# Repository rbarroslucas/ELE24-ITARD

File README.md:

# ITA Rocket Design — Eletrônica

Repositório com códigos, esquemáticos e materiais de referência antigos do time de Eletrônica da ITA Rocket Design.

> Participação como membro (2023) e líder de eletrônica (2024 – meados de 2025).
> Os arquivos de PCB no KiCad **não foram publicados**.

---

## Estrutura do repositório

```
.
├── ELE2025/
│   ├── Código_ESP32/       # Módulo de telemetria (GPS + LoRa)
│   ├── Código_STM32/       # Placa principal de aviónica
│   ├── Minifogutes/        # Computador de voo para minifoguetes
│   ├── Receiver/           # Receptor LoRa em terra
│   ├── drop_test/          # Código para ensaio de impacto
│   └── Balanca/            # Software para ensaio estático de empuxo
├── PCB Design/
│   ├── Minifoguetes/       # Gerbers e esquemático (KiCad)
│   └── Transdutor/         # PCB do transmissor de pressão (KiCad)
├── Schematics/             # Esquemáticos em PDF (sistema ELE IPEV)
└── Exemplos/               # Códigos de referência
```

---

## Projetos

### Minifoguetes — Computador de Voo

Firmware para Arduino embarcado nos minifoguetes da equipe. Detecta decolagem por barômetro (BMP280), registra altitude e velocidade em cartão SD e aciona a recuperação (SKIB) automaticamente no apogeu.

**Hardware:** BMP280 · Cartão SD · LED · Buzzer · SKIB
**Arquivo:** `ELE2025/Minifogutes/minifog.ino`

```
Fluxo principal
├── calib()   — média inicial de altitude e velocidade no solo
├── solo()    — aguarda decolagem (Δh ≥ Hmin e |v| ≥ 1 m/s)
└── flight()  — registra dados e aciona SKIB no apogeu
```

---

### ELE2025 — Módulo ESP32 (Telemetria)

Responsável por coletar posição GPS e transmitir via LoRa (915 MHz) para a base em tempo real.

**Hardware:** ESP32 (Heltec) · GPS UART · LoRa 915 MHz · I2C
**Arquivos:** `ELE2025/Código_ESP32/Main/`

| Arquivo       | Função                                                             |
| ------------- | -------------------------------------------------------------------- |
| `Main.ino`  | Loop principal: lê GPS, monta pacote e envia via LoRa               |
| `GPS.ino`   | Leitura e parse do módulo GPS (latitude, longitude, altitude, hora) |
| `Radio.ino` | Configuração e envio LoRa                                          |
| `I2C.ino`   | Comunicação I2C com periféricos                                   |

---

### ELE2025 — Placa Principal STM32

Placa de aviónica com múltiplos sensores, comunicação SPI com o ESP32 e protocolo de instruções para controle de periféricos.

**Hardware:** STM32 · MPU9250 (IMU ×4) · BMP280 · HX711 (célula de carga) · Bateria · LED RGB · Buzzer · 6 chaves
**Arquivos:** `ELE2025/Código_STM32/Main/`

| Arquivo         | Função                                                   |
| --------------- | ---------------------------------------------------------- |
| `Main.ino`    | Setup e loop principal                                     |
| `MPU9250.ino` | Leitura do IMU (acelerômetro, giroscópio, magnetômetro) |
| `BMP280.ino`  | Leitura de pressão e altitude                             |
| `Hx711.ino`   | Leitura de célula de carga                                |
| `SPI.ino`     | Comunicação SPI com ESP32 via enum de instruções       |
| `Bat.ino`     | Monitoramento de tensão da bateria                        |

O protocolo SPI usa um enum de instruções (`Main.h`) para controlar todos os subsistemas remotamente.

---

### Receptor LoRa

Receptor em terra baseado em Heltec ESP32. Escuta na mesma frequência/configuração do transmissor e imprime os pacotes no Serial com RSSI e SNR.

**Arquivo:** `ELE2025/Receiver/receiver.ino`
**Frequência:** 915 MHz · SF7 · BW 125 kHz

---

### Balança — Ensaio Estático de Empuxo

Software Python para aquisição de dados durante ensaios estáticos do motor. Lê força (N) e tempo (ms) via serial, plota em tempo real e salva em CSV numerado automaticamente.

**Arquivo:** `ELE2025/Balanca/BalancaV3.4.py`
**Dependências:** `pyserial`, `matplotlib`

```bash
python BalancaV3.4.py
```

Os dados são salvos em `test/t<n>.csv`.

---

### Drop Test

Código de ensaio de impacto usando BMP280 para medir altitude e velocidade durante quedas controladas.

**Arquivos:** `ELE2025/drop_test/drop_test.ino`, `MedM.ino`

---

## PCBs

Os projetos KiCad **não estão publicados**. Os arquivos Gerber para fabricação estão disponíveis:

| PCB                     | Gerbers                                                         |
| ----------------------- | --------------------------------------------------------------- |
| Minifoguetes            | `PCB Design/Minifoguetes/minifoguetes/PCB/`                   |
| Transmissor de Pressão | `PCB Design/Transdutor/transmissor/pressure_transmissor_pcb/` |

---

## Esquemáticos

`Schematics/`— Sistema modular de aviónica composto por seis placas: Base, Energia, Interface, Processamento, Sensores e Telecom. Quase um cubesat 1u.

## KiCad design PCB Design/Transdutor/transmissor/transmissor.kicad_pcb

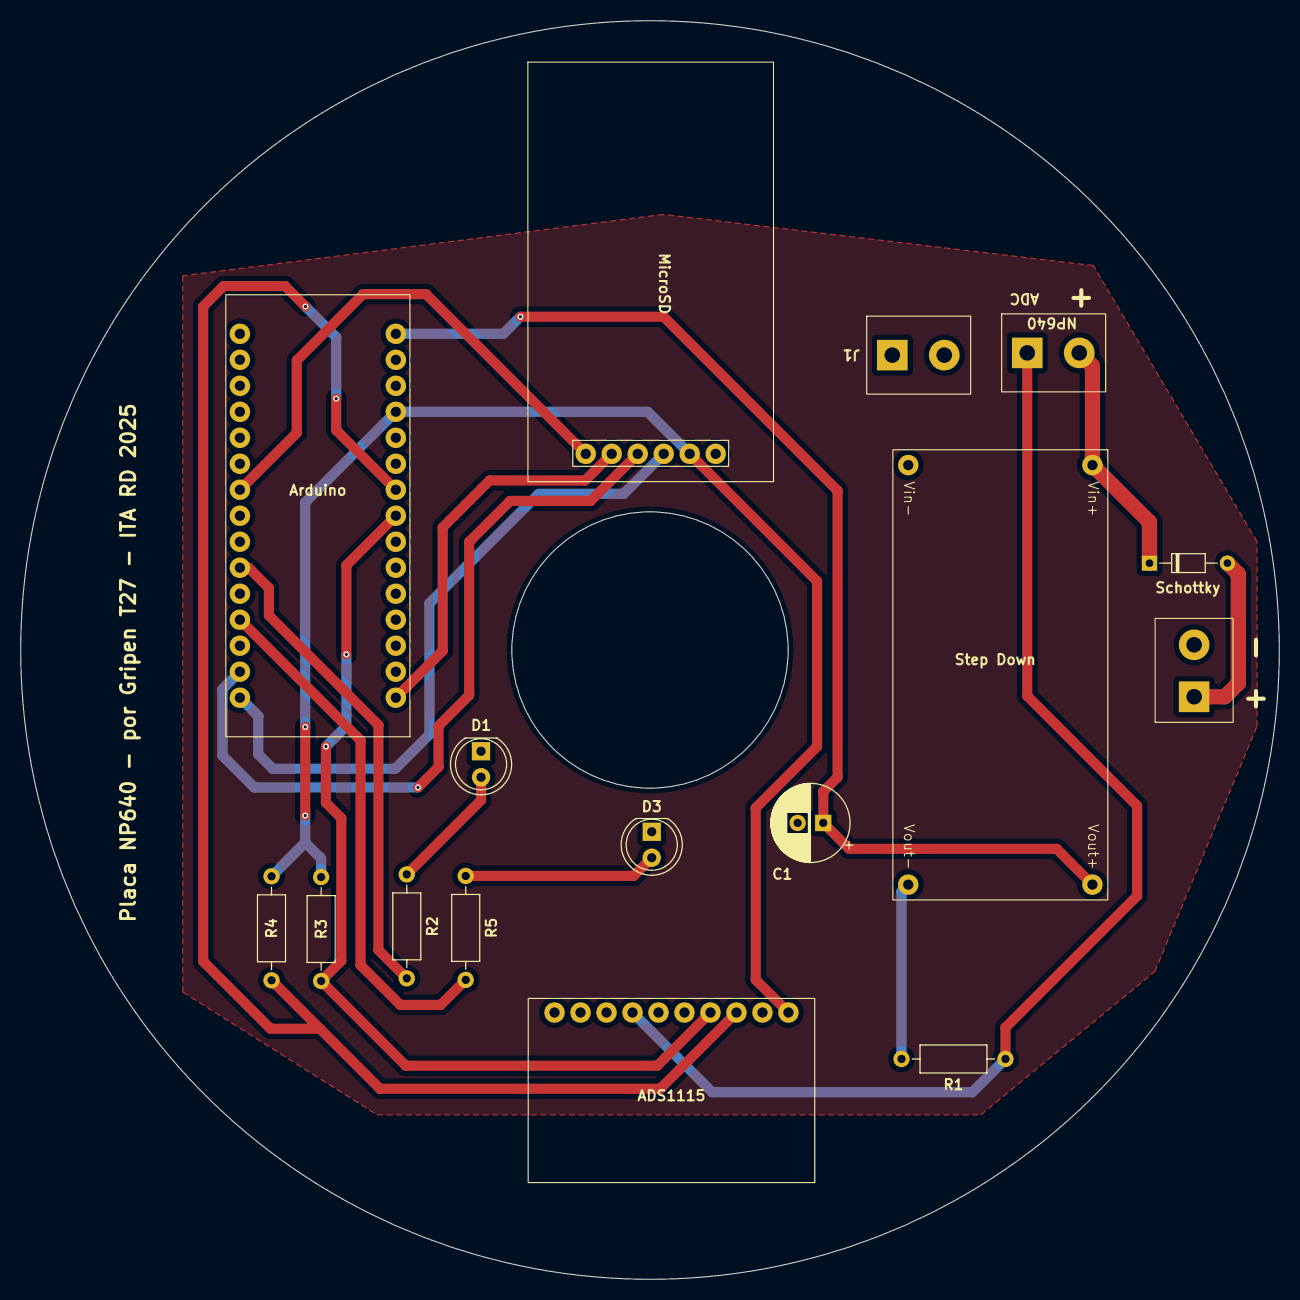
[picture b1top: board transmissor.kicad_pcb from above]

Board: 2 copper layers, 123.0 x 123.0 mm, 16 parts (0 on the bottom side), 16 nets.

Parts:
ADS1115: ADS1115
Arduino: Arduino Nano
C1: C; CP_Radial_D7.5mm_P2.50mm
D1, D3: LED; LED_D5.0mm
J1, J3: Screw_Terminal_01x02; Borne
MicroSD: MicroSD
NP640 : Screw_Terminal_01x02; Borne
R1: 200; R_Axial_DIN0207_L6.3mm_D2.5mm_P10.16mm_Horizontal
R2, R5: 1k; R_Axial_DIN0207_L6.3mm_D2.5mm_P10.16mm_Horizontal
R3, R4: 4.7k; R_Axial_DIN0207_L6.3mm_D2.5mm_P10.16mm_Horizontal
Schottky: D_Schottky; D_DO-34_SOD68_P7.62mm_Horizontal
Step Down: LM2596

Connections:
5V: ADS1115.1 (VCC), Arduino.12 (5V), MicroSD.5 (VCC), R3.1, R4.2
AIN0: ADS1115.7 (A0), NP640.1, R1.1
CS: Arduino.24 (D4), MicroSD.1 (CS)
GND: ADS1115.2 (GND), ADS1115.8 (A1), Arduino.14 (GND), Arduino.27 (GND), C1.2, D1.1 (K), D3.1 (K), J1.1, J1.2, J3.2, MicroSD.6 (GND), R1.2, Step Down.2 (Vin-), Step Down.3 (Vout-)
LED1: Arduino.21 (D7), R2.1
LED2: Arduino.19 (D9), R5.1
unnamed: ADS1115.3 (SCL), Arduino.9 (A5), R4.1
unnamed: ADS1115.4 (SDA), Arduino.8 (A4), R3.2
unnamed: Arduino.17 (D11), MicroSD.3 (MOSI)
unnamed: Arduino.16 (D12), MicroSD.4 (MISO)
unnamed: D1.2 (A), R2.2
unnamed: J3.1, Schottky.2 (A)
unnamed: D3.2 (A), R5.2
SCK: Arduino.1 (D13), MicroSD.2 (SCK)
Vbat+: NP640.2, Schottky.1 (K), Step Down.1 (Vin+)
Vin: Arduino.15 (VIN), C1.1, Step Down.4 (Vout+)

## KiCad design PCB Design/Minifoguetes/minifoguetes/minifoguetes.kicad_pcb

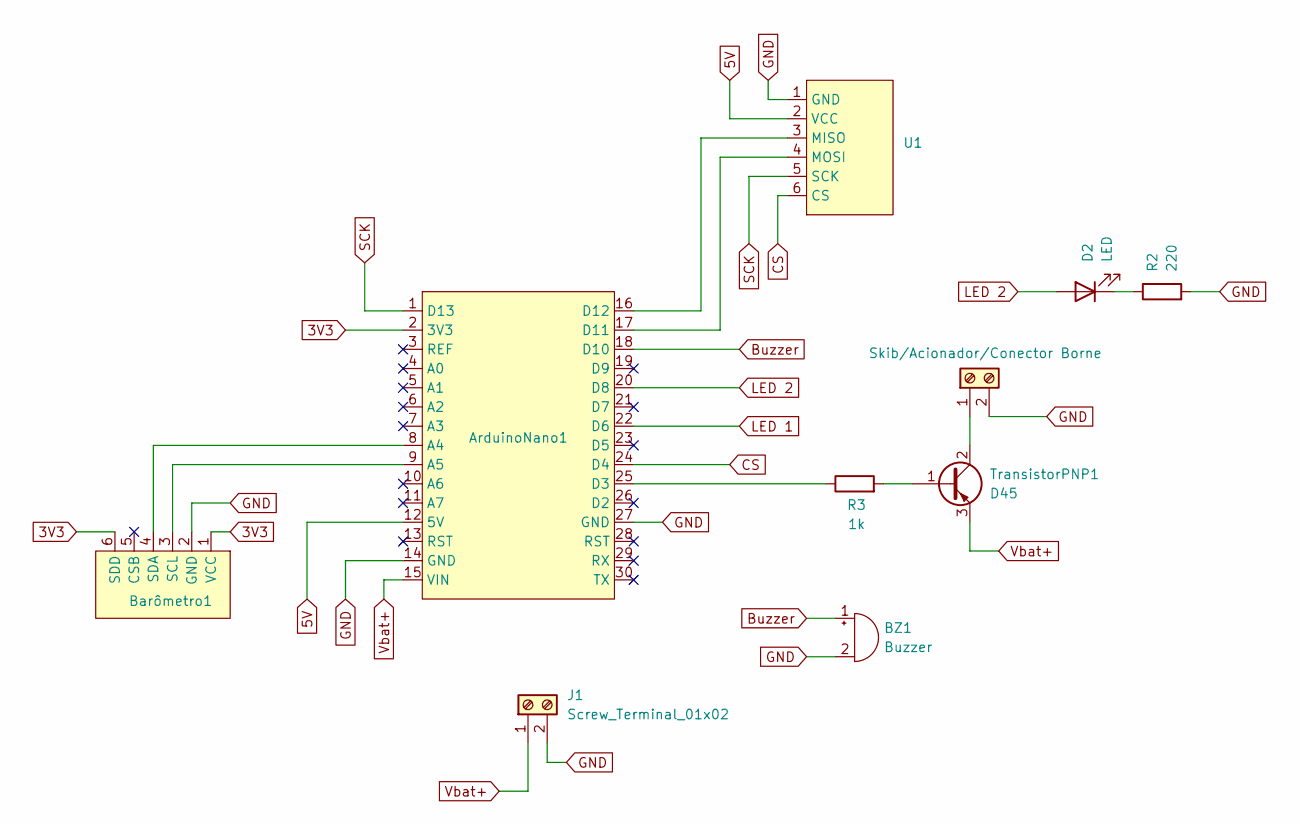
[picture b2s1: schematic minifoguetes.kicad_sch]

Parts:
ArduinoNano1: Arduino
BZ1: Buzzer; Buzzer_TDK_PS1240P02BT_D12.2mm_H6.5mm
Barômetro1: bmp280
D2: LED; LED_D5.0mm
J1: Screw_Terminal_01x02; TerminalBlock_bornier-2_P5.08mm
J3: Skib/Acionador/Conector Borne; TerminalBlock_bornier-2_P5.08mm
R2: 220; R_Axial_DIN0204_L3.6mm_D1.6mm_P7.62mm_Horizontal
R3: 1k; R_Axial_DIN0204_L3.6mm_D1.6mm_P7.62mm_Horizontal
TransistorPNP1: D45; TO-220_221A-09_ONS
U1: MicroSD

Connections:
3V3: ArduinoNano1.2 (3V3), Barômetro1.1 (VCC), Barômetro1.6 (SDD)
5V: ArduinoNano1.12 (5V), U1.2 (VCC)
Buzzer: ArduinoNano1.18 (D10), BZ1.1 (+)
CS: ArduinoNano1.24 (D4), U1.6 (CS)
GND: ArduinoNano1.14 (GND), ArduinoNano1.27 (GND), BZ1.2 (-), Barômetro1.2 (GND), J1.2, J3.2, R2.2, U1.1 (GND)
LED 1: ArduinoNano1.22 (D6)
LED 2: ArduinoNano1.20 (D8), D2.2 (A)
unnamed: ArduinoNano1.8 (A4), Barômetro1.4 (SDA)
unnamed: ArduinoNano1.9 (A5), Barômetro1.3 (SCL)
unnamed: ArduinoNano1.25 (D3), R3.1
unnamed: ArduinoNano1.17 (D11), U1.4 (MOSI)
unnamed: ArduinoNano1.16 (D12), U1.3 (MISO)
unnamed: D2.1 (K), R2.1
unnamed: J3.1, TransistorPNP1.2 (C)
unnamed: R3.2, TransistorPNP1.1 (B)
SCK: ArduinoNano1.1 (D13), U1.5 (SCK)
Vbat+: ArduinoNano1.15 (VIN), J1.1, TransistorPNP1.3 (E)

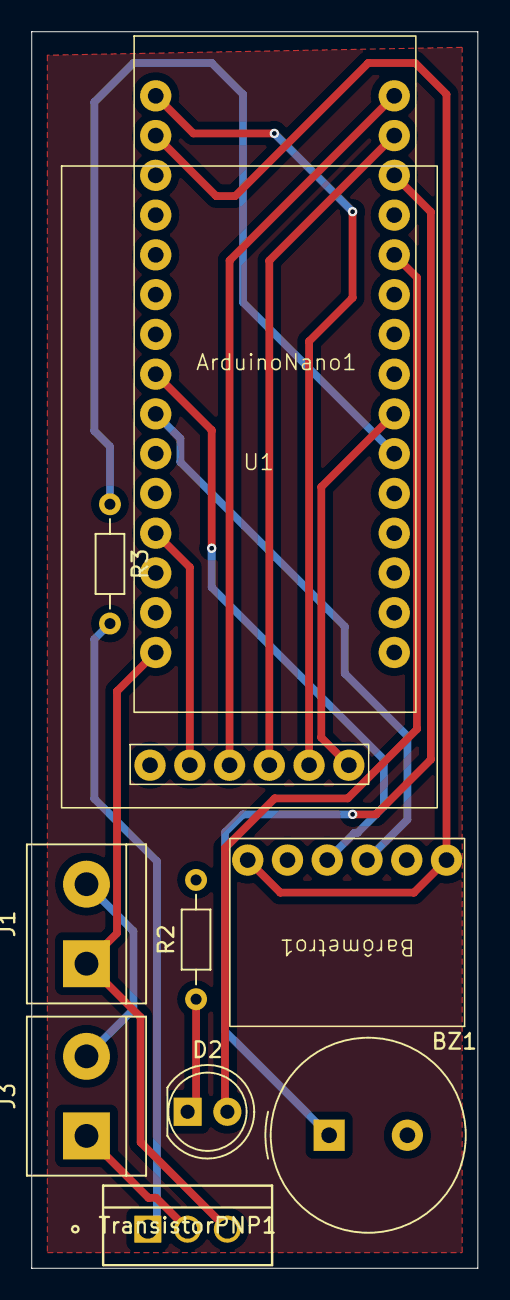
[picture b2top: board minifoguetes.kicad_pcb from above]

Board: 2 copper layers, 28.5 x 79.0 mm, 10 parts (0 on the bottom side), 16 nets.

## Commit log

2026-05-19 esqueci de adicionar os arquivos
